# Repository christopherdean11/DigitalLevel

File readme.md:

# Digital LED Level
Custom PCB for using an accelerometer as a level with LED indicators. Scope is small to encourage getting to the finish line but has enough hardware features to come up with createive software ideas. 

## Goals
Overall: Create a PCB from scratch that can display multiple LED patterns  
- [x] Select a MCU - STM32F030F4
- [x] Design a PCB
- [x] Fab the PCB
- [x] Populate the PCB
- [x] Code and test the PCB

## Vender Documentation
### Datasheets:
* MCU - [STM32F030F4](https://www.st.com/resource/en/datasheet/stm32f030f4.pdf), [Reference Manual](https://www.st.com/resource/en/reference_manual/dm00091010-stm32f030x4x6x8xc-and-stm32f070x6xb-advanced-armbased-32bit-mcus-stmicroelectronics.pdf)
* 3.3V LDO - [MIC5504-3.3](https://www.microchip.com/wwwproducts/en/MIC5504)
* Accelerometer - [ADXL343](https://www.analog.com/media/en/technical-documentation/data-sheets/ADXL343.pdf)
* Acceleromter Breakout [Adafruit ADXL343 Breakout](https://learn.adafruit.com/adxl343-breakout-learning-guide/downloads)

### Guides / App Notes / Manuals:
* [STM32 Boot Options](https://www.st.com/content/ccc/resource/technical/document/application_note/b9/9b/16/3a/12/1e/40/0c/CD00167594.pdf/files/CD00167594.pdf/jcr:content/translations/en.CD00167594.pdf)
* [Getting Started with STM32F030xx Hardware Development](https://www.st.com/content/ccc/resource/technical/document/application_note/91/66/2d/8c/f9/b5/47/55/DM00089834.pdf/files/DM00089834.pdf/jcr:content/translations/en.DM00089834.pdf)
* [STM32F3 Discovery User Manual](https://www.st.com/content/ccc/resource/technical/document/user_manual/8a/56/97/63/8d/56/41/73/DM00063382.pdf/files/DM00063382.pdf/jcr:content/translations/en.DM00063382.pdf) (Initially used as a programmer, later replaced with standalone ST-LINK V2 USB dongle)

## Design Process
See [Hardware Design](pcb/readme.md) for hardware design process.  
Software Design readme coming soon.

## Features
#### Hardware
* 9 LEDs
* STM32F0
* Acceleromter
* 2 push-buttons
  - 1 hardwired to GPIO
  - 1 wired through a jumper to a GPIO (shared with INT1 on accelerometer)

#### Software
* LED cycle patterns with speed and direction adjustable with push-buttons

---
## Ideas for rev1
* Add a switch on the vcc input 
* Add smt LED on 3V3
* Just get the thing professionally assembled
* Would be nice to power from batteries, perhaps need a nice connector for that
* micro usb for power in connector?
* input voltage protection
* want to be able to control LED brightness
  - could try to find a suitable LED driver
  - could just add a PMOS inline with Vled for pwm-ing
  - could pwm the GPIOs but I don't think that would wok because PWM-ing the GPIO would block execution unless it was hardware timed somehow

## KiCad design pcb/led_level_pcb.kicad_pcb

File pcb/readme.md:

# Hardware Design Process
## MCU Requirements
### Select an MCU
Initially thought about picking an STM32G0 series for low-cost, but after looking into it more, the STM32F0 series is not much more when buying low quantity, seems to be more popular, has extensive documentation, and the STM32F and STM32L series parts are already library components in Kicad.  
Another considerations was a package that lends itself to hand soldering.  With all of these in mind, I selected the [STM32F030F4](https://www.st.com/en/microcontrollers-microprocessors/stm32f030f4.html) in 20-pin TSSOP at approx. $1.23/unit.

###  I/O
This requires some time in STM Cube IDE to verify pinout and pin options to get a feel for what the board can look like.  We can easily get 8 GPIO outputs for LEDs with this MCU.  The [STM32F030F4](https://www.st.com/en/microcontrollers-microprocessors/stm32f030f4.html) comes in a 20pin TSSOP (this project will be hand soldered), with 12 GPIO available on PORTA + PB1 for 13 GPIO pins.
###  Programming
Another big item is how to program the MCU.  It looks like the STM32F030F4 has SWD (I beleive all ARM MCUs have this) support, so I should be able to connect with ST-LINK using SWD pins.  The F3 discovery board has an option to disconnect the actual dev board section from the ST-LINK section and use ST-LINK to program another board.  This will be a good starting point for programming. So the board will need to have the SWD pins broken out to headers.  

Tie BOOT0 to GND for normal operation and programming with SWD. See [this forum page](https://community.st.com/s/question/0D50X00009XkYDuSAN/hi-what-is-boot0-in-stm32).  Could tie it to a resitor to GND to leave door open to overdrive it if needed for some reason.  

The pinout for the SWD connector on the F3 Discovery board is available in [this document](https://www.st.com/content/ccc/resource/technical/document/user_manual/8a/56/97/63/8d/56/41/73/DM00063382.pdf/files/DM00063382.pdf/jcr:content/translations/en.DM00063382.pdf), page 16
Pins required: 
* VDD
* SWCLK
* GND
* SWDIO
* NRST - **NOTE:Solder bridge SB7 must be open to use NRST pin to control another device**

*Note: Eventually gave up with the F3 Discovery and orered a standalone ST-LINK V2 dongle, seems to just be easier*

## PCB Requirements:
- As small as reasonably possible to save cost
- series of LEDs in a row at one end
- SWD programming/debugging pins broken out
- At least 1 push button to cycle through LED options
- Acceleromter to do I2C comms and for LED patterns  

##  PCB Design Process:
* [x] Open CubeIDE to start a project with the STM32F030F4 and set up the pin configurations.
* [x] Add the MCU to a new design in Kicad.
* [x] Refer to the CubeIDE for the desired pin configuration.  Break out the SWD pins to headers and strap the BOOT pin.
* [x] Add some LEDs and a push button and wire it up.
* [x] Research and find an acceptable accelerometer.  Low cost I2C capable and hand-solerable.
* [x] Research and select a 3.3V regulator to power from 5V.

### Power
Plan is to power the board with 5V DC from a wall wart and regulate it to 3.3V.  Since this isn't powered by a battery, power efficiency isn't really a concern on this project (save that futuer versions), so an LDO will be fine, gets the job done and is dead simple to add to a PCB.  
#### Selecting 3.3V Regulator:
Just filter on digikey/mouser for 3.3V LDO. Found [MIC5504-3.3YM5](https://www.microchip.com/wwwproducts/en/MIC5504) for 3.3V at 300mA and 2% initial accuracy. VIN up to 5.5V. 
#### LED Power Consumption
9 LEDs at 15mA = 135mA  
Total allowed GPIO sourcing current for STM32F030F4 is 80mA (see page 44 in datasheet)  
*Redesigned board so LEDs are powered by the VDD rail and turned on off by GPIOs with an NMOS.*

### Acceleromoter
Needed a breakout board because all acceleromters have packages that do not lend themselves to hand-soldering.  The ADXL343 breakout from Adafruit is reasonbly priced and uses a quality acceleromter. 
Some notes: 
* Has a level shifter on board, may need to remove/jump over those but do not expect a problem
* See pg 16 of [ADXL3434 datasheet](https://www.analog.com/media/en/technical-documentation/data-sheets/ADXL343.pdf) for I2C addresses and address for Read/Write

| SDO/ALT_ADDRESS Pin | 7 bit address | Read Address | Write Address |  
| --- | --- | ---- | --- |  
| GND | 0x53| 0xA6 | 0xA7 |

I2C address are 7-bit, and the least-signficant bit (LSB) is used to determine if the transaction is a read or write.

## PCB Layout
Begin layout of the design and revise as needed.
### Layout Process
1. Get everything in roughly the desired position. See how it looks, revise layout and schematic as needed.
   - I want all the LEDs in a nice row on the edge, so I changed the schematic to put LED current limit resistors between LED and NMOS and moved the current sense solder bridges for LED1 and LED5 for the same reason.  
1. Move on to routing power and ground after initial revisions are complete and rough layout is acceptable.
   - 2 Layer board
   - Ground plane as bottom layer, only use for routing when necessary to jump under existing traces
   - Run power along the edge of the board for LEDs and SW1, SW2, and wrap around to power acceleromter
   - This is not a high-speed or high-precision board, routing will be as good as it can be with 2 layers
## PCB Bring-Up Plan
Populate minimally requried components to get a program onto the board and show a sign of life.  
* Header pins, U1, U2, Boot resistor, decoupling caps, and LED2
* Run a program to blink LED2 to prove communication

Once that is working populate remainder of board and run a progressive blink routine to validate each LED.

## Experience Notes
* Almost forgot to add decoupling caps, researched and added those to the design as per the "Getting Started with STM32F030xx Hardware Development" link above.  
* Just noticed there is a "hand-solder" optional footprint for SMT components in KiCAD, and since I plan to hand solder, I will have to change all the footprints to those or I will probably wish I did.
* Board ordered on Feb 28 via oshpark
* Parts ordered on Feb 29 via mouser  

---

## Board Bring-up

*Eventually resolved these issues below and can talk to the board. Still not clear what the fix truly was, but I bought a standalone ST-LINK V2 USB dongle, updated STM CubeIDE to the latest, and completely discarded the Cube code project and started a Cube project, and all seems to be well.  The program downloads to the micro and the debugger works. Original debugging notes kept here.*

#### Original Debug Notes
* Trying to program using F3Discovery board as an ST-LINK and getting 

> Error message from debugger back end:  
> Load failed  
> Failed to execute MI command:  
> load /Users/christopherdean/Dev/stm32/LED_Level/code/Debug/Digital_Level.elf   
>  
> Error message from debugger back end:  
> Load failed  
> Load failed  

* Checked current on 3V3 rail (not using 3.3V regulator) and see it at ~1.3mA for a second or two, and then jump to ~1.8mA or 2mA
* [This schematic](https://easyeda.com/r3bers/STM32F103C8T6-Test-Board) shows pullup/down resistors on SWCLKS/SWDIO 
  - other posts online say the uc should have internal pullup/downs that are sufficient..

* Command to run the debugger from command line:
navigate to  
```
/Applications/STM32CubeIDE.app/Contents/Eclipse/plugins/com.st.stm32cube.ide.mcu.externaltools.stlink-gdb-server.macos64_1.3.0.202002181050/tools/bin
```
and run
```
./ST-LINK_gdbserver -d -v -cp /Applications/STM32CubeIDE.app/Contents/Eclipse/plugins/com.st.stm32cube.ide.mcu.externaltools.cubeprogrammer.macos64_1.3.0.202002181050/tools/bin
```

When I run it to program my board:
```
STMicroelectronics ST-LINK GDB server. Version 5.5.0
Copyright (c) 2019, STMicroelectronics. All rights reserved.

Starting server with the following options:
        Persistent Mode            : Disabled
        Logging Level              : 31
        Listen Port Number         : 61234
        Status Refresh Delay       : 15s
        Verbose Mode               : Enabled
        SWD Debug                  : Enabled

Target connection mode: Default
Target connection failed. Try connecting under reset
Target connection failed
Target unknown error 19

Error in initializing ST-LINK device.
Reason: Unknown. Please check power and cabling to target.
```

When I install the jumpers on the F3DISCOVERY board to use the ST-LINK to program the discovery board (and not just as an ST-LINK for external things), I see this:
```
STMicroelectronics ST-LINK GDB server. Version 5.5.0
Copyright (c) 2019, STMicroelectronics. All rights reserved.

Starting server with the following options:
        Persistent Mode            : Disabled
        Logging Level              : 31
        Listen Port Number         : 61234
        Status Refresh Delay       : 15s
        Verbose Mode               : Enabled
        SWD Debug                  : Enabled

Target connection mode: Default
Hardware watchpoint supported by the target 
COM frequency = 4000 kHz
ST-LINK Firmware version : V2J36M26
Device ID: 0x422
PC: 0x80007f8
ST-LINK device status: HALT_MODE
ST-LINK detects target voltage = 2.91 V
ST-LINK device status: HALT_MODE
ST-LINK device initialization OK
Waiting for debugger connection...
Waiting for connection on port 61234...
```
while it wait for a `gdb` process to connect to it

Maybe my microcontrollers are toasted?
Maybe next step is to solder one to a breakout board and try to program it on a breadboard?

Borrowed an STM32 USB programmer from a friend, got a new error about part is LOCKUP and debugger timed out.  Thought maybe finally clicking on the "Update CubeIDE" button might help. Get 1.4.2 installed and now the debugger won't even startup, just opens a window with 
```
ST-LINK Server is required to start the debug session. Download from st.com
```
Ok. Download. Install. No change. Restart the IDE. No change. :( 
This forum post suggests downgrading from 1.4.2 to 1.4.0 to get it to work. Ugh.
https://community.st.com/s/question/0D53W00000GWQKn/how-can-stlink-server-be-installed-for-use-by-stm32cubeide-

Tried to manually start the gdb session from the terminal with help here https://jacobmossberg.se/posts/2017/01/17/use-gdb-on-arm-assembly-program.html
it appeared to work and even saw `ST-LINK device status: RUN_MODE` but my board was still not working, perhaps a fundamental HW issue I just don't see. 

NRST pin is tied to the NRST pin on the SWD jumper but otherwise is floating.  It is supposed to be connected to a 40k ohm (typ) pullup internally.  There is a recommendation for a 0.1uF external capacitor to prevent parasitic resets, which is missing from the PCB design.  

#### Other Debugging Ideas
Maybe try the i2c lines as usart data lines for programming?
http://eleceng.dit.ie/frank/arm/STM32F030ISP/index.html

Maybe try after driving boot pin high:
https://electronics.stackexchange.com/questions/410386/stm32f0-boot0-pin-and-swd-programming

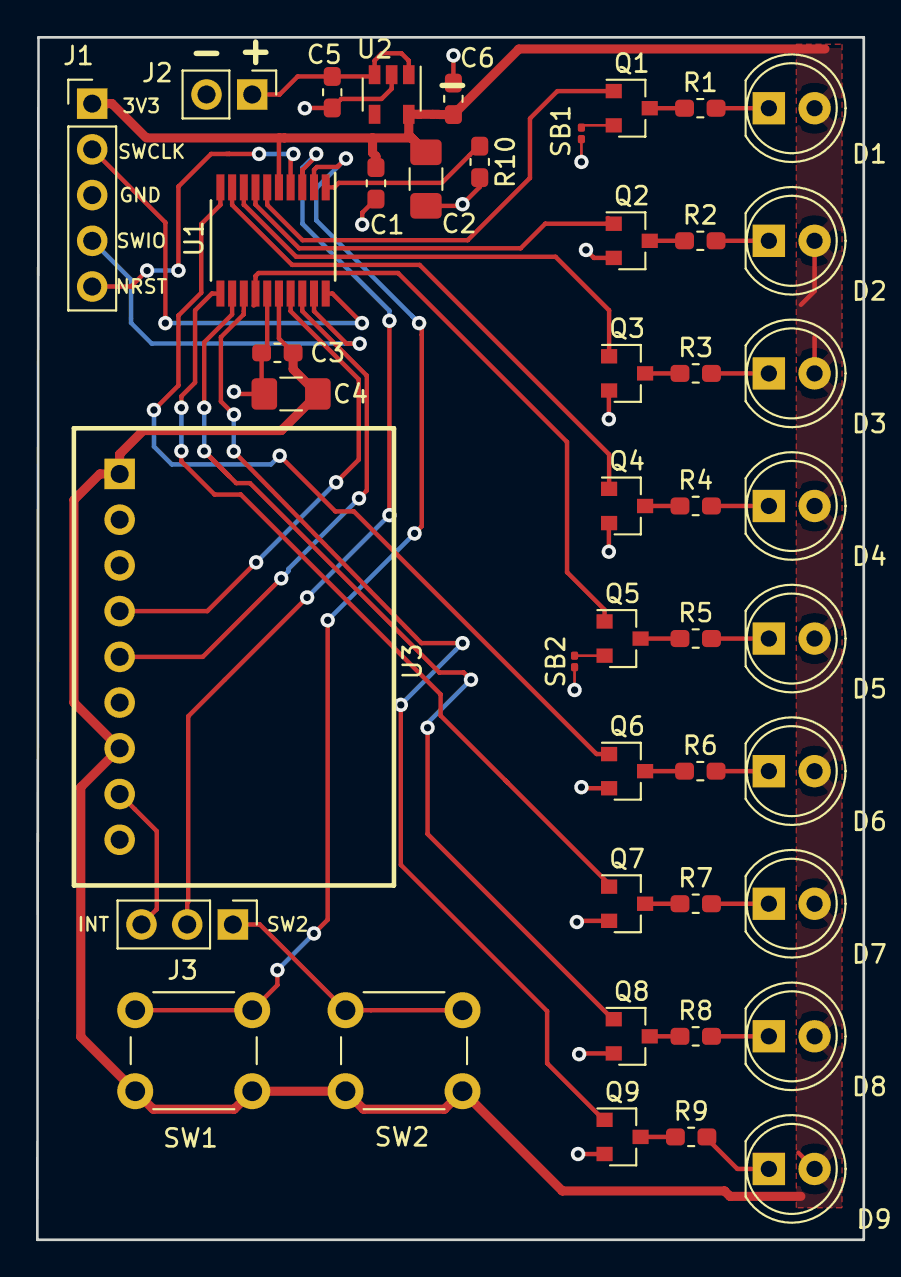
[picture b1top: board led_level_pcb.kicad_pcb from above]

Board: 2 copper layers, 45.9 x 66.8 mm, 44 parts (0 on the bottom side), 42 nets.

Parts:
C1: 100n; C_0603_1608Metric_Pad1.05x0.95mm_HandSolder
C2: 4.7u; C_1206_3216Metric_Pad1.42x1.75mm_HandSolder
C3: 10n; C_0603_1608Metric_Pad1.05x0.95mm_HandSolder
C4: 1u; C_1206_3216Metric_Pad1.42x1.75mm_HandSolder
C5, C6: 1u; C_0603_1608Metric_Pad1.05x0.95mm_HandSolder
D1, D2, D3, D4, D5, D6, D7, D8, D9: LED; LED_D5.0mm
J1: Conn_SWD; PinHeader_1x05_P2.54mm_Vertical
J2: Conn_VIN; PinHeader_1x02_P2.54mm_Vertical
J3: Conn_SW_INT; PinHeader_1x03_P2.54mm_Vertical
Q1, Q2, Q3, Q4, Q5, Q6, Q7, Q8, Q9: 2N7002; SOT-23
R1, R2, R3, R4, R6, R7, R8, R9: 100; R_0603_1608Metric_Pad1.05x0.95mm_HandSolder
R5: 82; R_0603_1608Metric_Pad1.05x0.95mm_HandSolder
R10: R; R_0603_1608Metric_Pad1.05x0.95mm_HandSolder
SB1, SB2: 0; R_0201_0603Metric
SW1, SW2: SW_Push; SW_PUSH_6mm
U1: STM32F030F4Px; TSSOP-20_4.4x6.5mm_P0.65mm
U2: MIC5504-3.3YM5; SOT-23-5
U3: ADXL343_Breakout

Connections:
+3V3: C1.1, C2.1, C3.1, C4.1, C6.1, D1.2, D2.2, D3.2, D4.2, D5.2, D6.2, D7.2, D8.2, D9.2, J1.1, SW1.1, SW2.1, U1.5, U1.16, U2.5, U3.1, U3.7
/I2C_SCL: U1.17, U3.4
/I2C_SDA: U1.18, U3.5
/LED1: Q1.1, U1.6
/LED2: Q2.1, U1.7
/LED3: Q3.1, U1.8
/LED4: Q4.1, U1.9
/LED5: Q5.1, U1.14
/LED6: Q6.1, U1.10
/LED7: Q7.1, U1.11
/LED8: Q8.1, U1.12
/LED9: Q9.1, U1.13
/NRST: J1.5, U1.4
/SWCLK: J1.2, U1.20
/SWDIO: J1.4, U1.19
/VIN: C5.1, J2.1, U2.1, U2.3
GND: C1.2, C2.2, C3.2, C4.2, C5.2, C6.2, J1.3, J2.2, Q2.2, Q3.2, Q4.2, Q6.2, Q7.2, Q8.2, Q9.2, R10.2, SB1.1, SB2.1, U1.15, U2.2, U3.3, U3.6
unnamed: D1.1, R1.2
unnamed: D2.1, R2.2
unnamed: D3.1, R3.2
unnamed: D4.1, R4.2
unnamed: D5.1, R5.2
unnamed: D6.1, R6.2
unnamed: D7.1, R7.2
unnamed: D8.1, R8.2
unnamed: D9.1, R9.2
unnamed: J3.1, SW2.2
unnamed: J3.2, U1.3
unnamed: J3.3, U3.8
unnamed: Q1.2, SB1.2
unnamed: Q1.3, R1.1
unnamed: Q2.3, R2.1
unnamed: Q3.3, R3.1
unnamed: Q4.3, R4.1
unnamed: Q5.2, SB2.2
unnamed: Q5.3, R5.1
unnamed: Q6.3, R6.1
unnamed: Q7.3, R7.1
unnamed: Q8.3, R8.1
unnamed: Q9.3, R9.1
unnamed: R10.1, U1.1
unnamed: SW1.2, U1.2

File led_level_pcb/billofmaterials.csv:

"Id";"Designator";"Package";"Quantity";"Designation";"Supplier and ref";
1;"R10";"R_0603_1608Metric_Pad1.05x0.95mm_HandSolder";1;"R";;;
2;"R9,R8,R7,R6,R4,R3,R2,R1";"R_0603_1608Metric_Pad1.05x0.95mm_HandSolder";8;"100";;;
3;"R5";"R_0603_1608Metric_Pad1.05x0.95mm_HandSolder";1;"82";;;
4;"U3";"ADXL343_Breakout";1;"ADXL343_Breakout";;;
5;"U2";"SOT-23-5";1;"MIC5504-3.3YM5";;;
6;"D9,D1,D2,D3,D4,D5,D6,D7,D8";"LED_D5.0mm";9;"LED";;;
7;"J1";"PinHeader_1x05_P2.54mm_Vertical";1;"Conn_SWD";;;
8;"J2";"PinHeader_1x02_P2.54mm_Vertical";1;"Conn_VIN";;;
9;"Q1,Q2,Q3,Q4,Q5,Q6,Q7,Q8,Q9";"SOT-23";9;"2N7002";;;
10;"SW1,SW2";"SW_PUSH_6mm";2;"SW_Push";;;
11;"U1";"TSSOP-20_4.4x6.5mm_P0.65mm";1;"STM32F030F4Px";;;
12;"J3";"PinHeader_1x03_P2.54mm_Vertical";1;"Conn_SW_INT";;;
13;"C1";"C_0603_1608Metric_Pad1.05x0.95mm_HandSolder";1;"100n";;;
14;"C2";"C_1206_3216Metric_Pad1.42x1.75mm_HandSolder";1;"4.7u";;;
15;"C3";"C_0603_1608Metric_Pad1.05x0.95mm_HandSolder";1;"10n";;;
16;"C4";"C_1206_3216Metric_Pad1.42x1.75mm_HandSolder";1;"1u";;;
17;"C5,C6";"C_0603_1608Metric_Pad1.05x0.95mm_HandSolder";2;"1u";;;
18;"SB1,SB2";"R_0201_0603Metric";2;"0";;;

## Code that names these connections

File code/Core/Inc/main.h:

/* USER CODE BEGIN Header */
/**
  ******************************************************************************
  * @file           : main.h
  * @brief          : Header for main.c file.
  *                   This file contains the common defines of the application.
  ******************************************************************************
  * @attention
  *
  * <h2><center>&copy; Copyright (c) 2020 STMicroelectronics.
  * All rights reserved.</center></h2>
  *
  * This software component is licensed by ST under BSD 3-Clause license,
  * the "License"; You may not use this file except in compliance with the
  * License. You may obtain a copy of the License at:
  *                        opensource.org/licenses/BSD-3-Clause
  *
  ******************************************************************************
  */
/* USER CODE END Header */

/* Define to prevent recursive inclusion -------------------------------------*/
#ifndef __MAIN_H
#define __MAIN_H

#ifdef __cplusplus
extern "C" {
#endif

/* Includes ------------------------------------------------------------------*/
#include "stm32f0xx_hal.h"

/* Private includes ----------------------------------------------------------*/
/* USER CODE BEGIN Includes */

/* USER CODE END Includes */

/* Exported types ------------------------------------------------------------*/
/* USER CODE BEGIN ET */

/* USER CODE END ET */

/* Exported constants --------------------------------------------------------*/
/* USER CODE BEGIN EC */

/* USER CODE END EC */

/* Exported macro ------------------------------------------------------------*/
/* USER CODE BEGIN EM */

/* USER CODE END EM */

/* Exported functions prototypes ---------------------------------------------*/
void Error_Handler(void);

/* USER CODE BEGIN EFP */

/* USER CODE END EFP */

/* Private defines -----------------------------------------------------------*/
#define SW0_Pin GPIO_PIN_0
#define SW0_GPIO_Port GPIOF
#define SW0_EXTI_IRQn EXTI0_1_IRQn
#define SW1_Pin GPIO_PIN_1
#define SW1_GPIO_Port GPIOF
#define SW1_EXTI_IRQn EXTI0_1_IRQn
#define LED1_Pin GPIO_PIN_0
#define LED1_GPIO_Port GPIOA
#define LED2_Pin GPIO_PIN_1
#define LED2_GPIO_Port GPIOA
#define LED3_Pin GPIO_PIN_2
#define LED3_GPIO_Port GPIOA
#define LED4_Pin GPIO_PIN_3
#define LED4_GPIO_Port GPIOA
#define LED6_Pin GPIO_PIN_4
#define LED6_GPIO_Port GPIOA
#define LED7_Pin GPIO_PIN_5
#define LED7_GPIO_Port GPIOA
#define LED8_Pin GPIO_PIN_6
#define LED8_GPIO_Port GPIOA
#define LED9_Pin GPIO_PIN_7
#define LED9_GPIO_Port GPIOA
#define LED5_Pin GPIO_PIN_1
#define LED5_GPIO_Port GPIOB
/* USER CODE BEGIN Private defines */

/* USER CODE END Private defines */

#ifdef __cplusplus
}
#endif

#endif /* __MAIN_H */

/************************ (C) COPYRIGHT STMicroelectronics *****END OF FILE****/

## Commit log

2020-10-07 board rev 0 as built
2020-10-07 updated notes
2020-10-07 rename notes.md to readme.md
2020-10-08 add cart from mouser order
2020-10-10 replace code with new project files
2020-10-13 rename led_level_pcb to pcb
2020-10-14 cleanup main
2020-10-31 clean up and split into files, get ax, ay, az
2020-10-31 update gitignore
2020-10-31 got accel data on leds, bugfix in LED_disableAll
2020-11-15 add schematic pdf
2020-12-12 add more accelerometer functions
